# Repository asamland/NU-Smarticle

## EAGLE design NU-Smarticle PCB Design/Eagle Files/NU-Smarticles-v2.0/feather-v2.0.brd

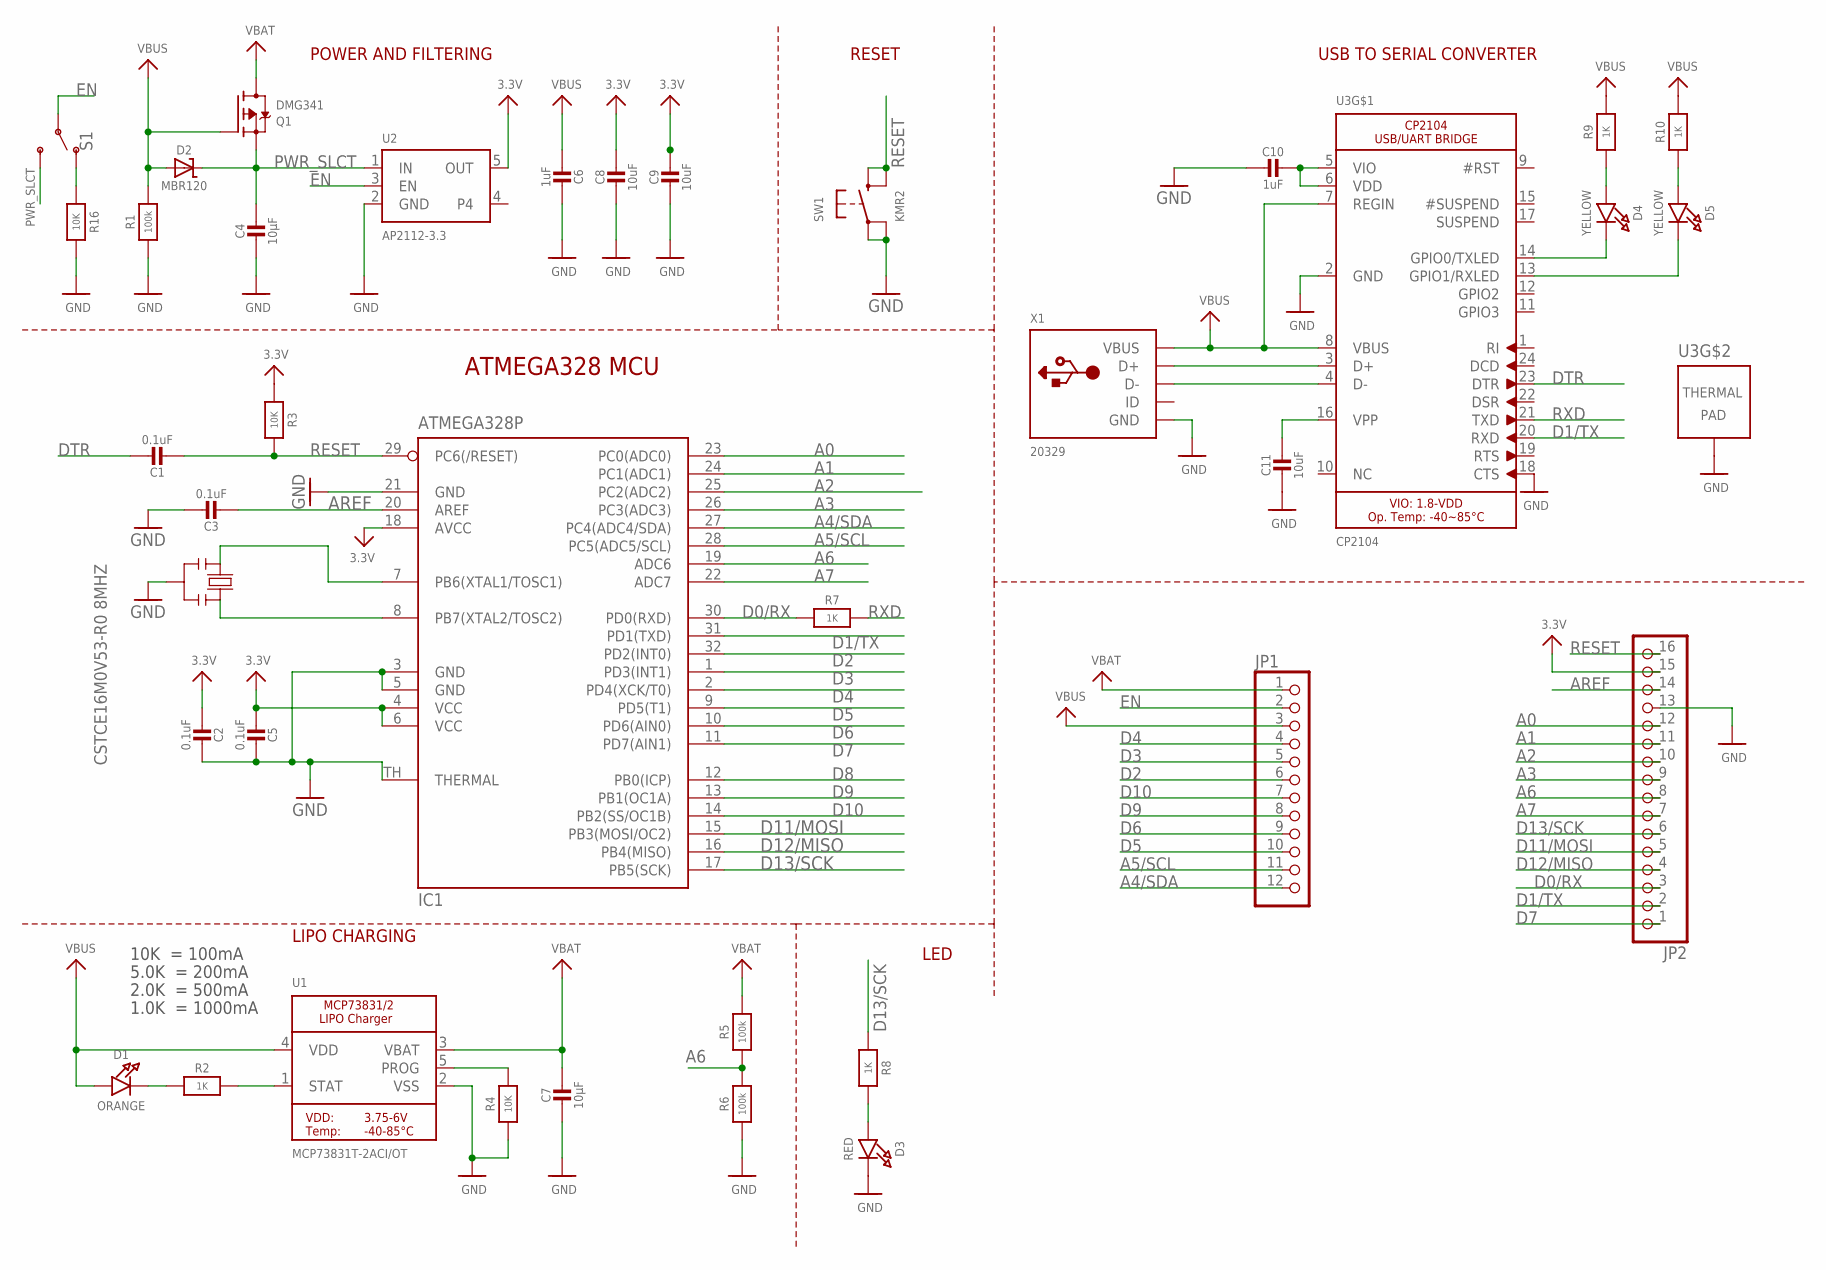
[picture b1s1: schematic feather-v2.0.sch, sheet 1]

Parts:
C1, C2, C3, C5: 0.1uF; _0603MP
C4, C7: 10µF; _0603MP
C6, C10: 1uF; _0603MP
C8, C9, C11: 10uF; _0603MP
D1: ORANGE; CHIPLED_0603_NOOUTLINE
D2: MBR120; SOD-323
D3: RED; CHIPLED_0603_NOOUTLINE
D4, D5: YELLOW; CHIPLED_0603_NOOUTLINE
IC1: ATMEGA328P; MLF32-TH
JP1: HEADER-1X12; 1X12_ROUND
JP2: HEADER-1X16ROUND; 1X16_ROUND
Q1: DMG341; SOT23-R
R1, R5, R6: 100k; _0603MP
R2, R7, R8, R9, R10: 1K; _0603MP
R3, R4, R16: 10K; _0603MP
S1: SWITCH-SPDT-SMD-RIGHT-ANGLE; SWITCH_SPST_SMD_A
SW1: KMR2; BTN_KMR2_4.6X2.8
U1: MCP73831T-2ACI/OT; SOT23-5
U2: AP2112-3.3; SOT23-5
U3: CP2104; QFN24_4MM_SMSC
X1: 20329; 4UCONN_20329_V2
Y1: CSTCE16M0V53-R0 8MHZ; RESONATOR

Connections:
3.3V: C2.2, C5.2, C8.1, C9.1, IC1.4 (VCC), IC1.6 (VCC), IC1.18 (AVCC), JP2.15, R3.2, U2.5 (OUT); also elsewhere on the board
A0: IC1.23 (PC0(ADC0)), JP2.12; also elsewhere on the board
A1: IC1.24 (PC1(ADC1)), JP2.11; also elsewhere on the board
A2: IC1.25 (PC2(ADC2)), JP2.10; also elsewhere on the board
A3: IC1.26 (PC3(ADC3)), JP2.9; also elsewhere on the board
A4/SDA: IC1.27 (PC4(ADC4/SDA)), JP1.12
A5/SCL: IC1.28 (PC5(ADC5/SCL)), JP1.11
A6: IC1.19 (ADC6), JP2.8, R5.1, R6.2
A7: IC1.22 (ADC7), JP2.7
AREF: C3.2, IC1.20 (AREF), JP2.14
D0/RX: IC1.30 (PD0(RXD)), JP2.3, R7.1
D1/TX: IC1.31 (PD1(TXD)), JP2.2, U3.20 (RXD)
D2: IC1.32 (PD2(INT0)), JP1.6; also elsewhere on the board
D3: IC1.1 (PD3(INT1)), JP1.5; also elsewhere on the board
D4: IC1.2 (PD4(XCK/T0)), JP1.4; also elsewhere on the board
D5: IC1.9 (PD5(T1)), JP1.10
D6: IC1.10 (PD6(AIN0)), JP1.9
D7: IC1.11 (PD7(AIN1)), JP2.1; also elsewhere on the board
D8: IC1.12 (PB0(ICP))
D9: IC1.13 (PB1(OC1A)), JP1.8
D10: IC1.14 (PB2(SS/OC1B)), JP1.7; also elsewhere on the board
D11/MOSI: IC1.15 (PB3(MOSI/OC2)), JP2.5
D12/MISO: IC1.16 (PB4(MISO)), JP2.4
D13/SCK: IC1.17 (PB5(SCK)), JP2.6, R8.1
DTR: C1.1, U3.23 (DTR)
EN: JP1.2, S1.2, U2.3 (EN)
GND: C2.1, C3.1, C4.2, C5.1, C6.1, C7.2, C8.2, C9.2, C10.2, C11.2, D3.C, IC1.3 (GND), IC1.5 (GND), IC1.21 (GND), IC1.TH (THERMAL), JP2.13, R1.1, R4.1, R6.1, R16.1, SW1.A, SW1.A' (P1), U1.2 (VSS), U2.2 (GND), U3.2 (GND), U3.18 (CTS), U3.THERM (TP), X1.BASE@1 (GND), X1.BASE@2 (GND), X1.GND, X1.SPRT@1 (GND), X1.SPRT@2 (GND), X1.SPRT@3 (GND), X1.SPRT@4 (GND), Y1.2; also elsewhere on the board
unnamed: D1.C, R2.1
unnamed: U3.3 (D+), X1.D+
unnamed: R2.2, U1.1 (STAT)
unnamed: R4.2, U1.5 (PROG)
unnamed: D3.A, R8.2
unnamed: U3.4 (D-), X1.D-
unnamed: R16.2, S1.1 (O)
unnamed: D5.A, R10.1
unnamed: D4.A, R9.1
unnamed: C10.1, U3.5 (VIO), U3.6 (VDD)
unnamed: C11.1, U3.16 (VPP)
PWR_SLCT: C4.1, D2.C, Q1.2 (S), S1.3 (S), U2.1 (IN)
RESET: C1.2, IC1.29 (PC6(/RESET)), JP2.16, R3.1, SW1.B (S), SW1.B' (S1)
RXD: R7.2, U3.21 (TXD)
RXLED: D5.C, U3.13 (GPIO1/RXLED)
TXLED: D4.C, U3.14 (GPIO0/TXLED)
VBAT: C7.1, JP1.1, Q1.3 (D), R5.2, U1.3 (VBAT); also elsewhere on the board
VBUS: C6.2, D1.A, D2.A, JP1.3, Q1.1 (G), R1.2, R9.2, R10.2, U1.4 (VDD), U3.7 (REGIN), U3.8 (VBUS), X1.VBUS
XTAL1: IC1.8 (PB7(XTAL2/TOSC2)), Y1.3
XTAL2: IC1.7 (PB6(XTAL1/TOSC1)), Y1.1

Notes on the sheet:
POWER AND FILTERING
RESET
10K = 100mA
5.0K = 200mA
2.0K = 500mA
1.0K = 1000mA
USB TO SERIAL CONVERTER
LIPO CHARGING
LED
ATMEGA328 MCU

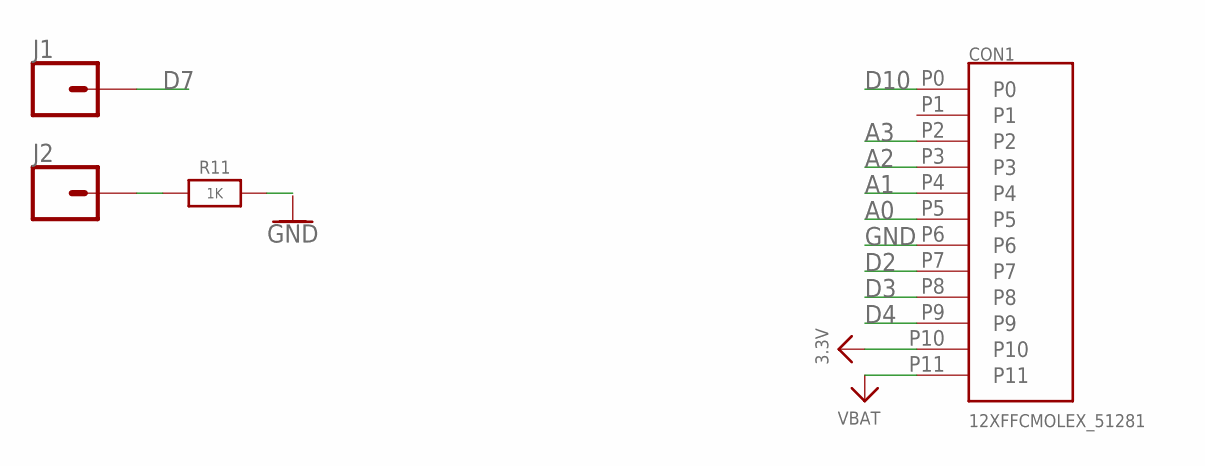
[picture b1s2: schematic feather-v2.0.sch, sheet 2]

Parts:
CON1: 12XFFCMOLEX_51281; MOLEX_51281-1294
J1, J2: CONN_01PTH_NO_SILK_YES_STOP; 1X01_NO_SILK
R11: 1K; _0603MP

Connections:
3.3V: CON1.P10; also elsewhere on the board
A0: CON1.P5; also elsewhere on the board
A1: CON1.P4; also elsewhere on the board
A2: CON1.P3; also elsewhere on the board
A3: CON1.P2; also elsewhere on the board
D2: CON1.P7; also elsewhere on the board
D3: CON1.P8; also elsewhere on the board
D4: CON1.P9; also elsewhere on the board
D7: J1.1; also elsewhere on the board
D10: CON1.P0; also elsewhere on the board
GND: CON1.P6; also elsewhere on the board
unnamed: J2.1, R11.1
VBAT: CON1.P11; also elsewhere on the board

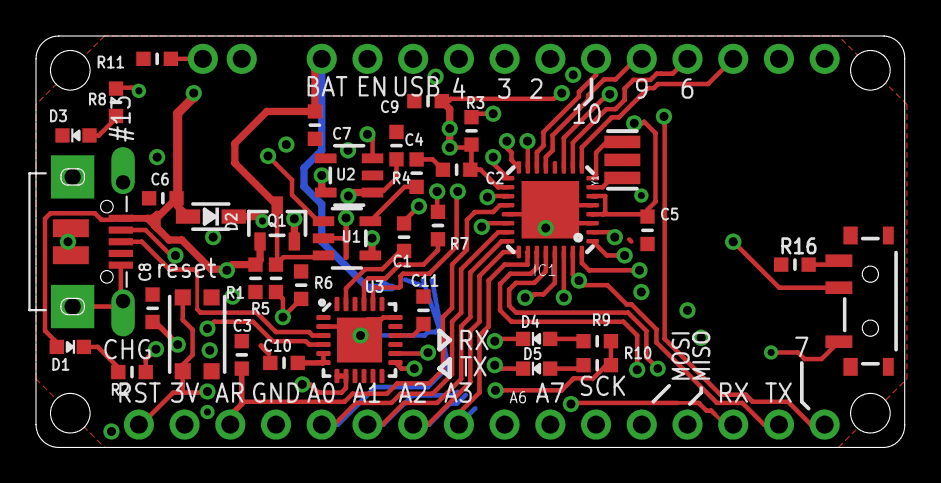
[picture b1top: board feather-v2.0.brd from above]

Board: 4 copper layers, 48.3 x 22.9 mm, 42 parts (1 on the bottom side), 47 nets.

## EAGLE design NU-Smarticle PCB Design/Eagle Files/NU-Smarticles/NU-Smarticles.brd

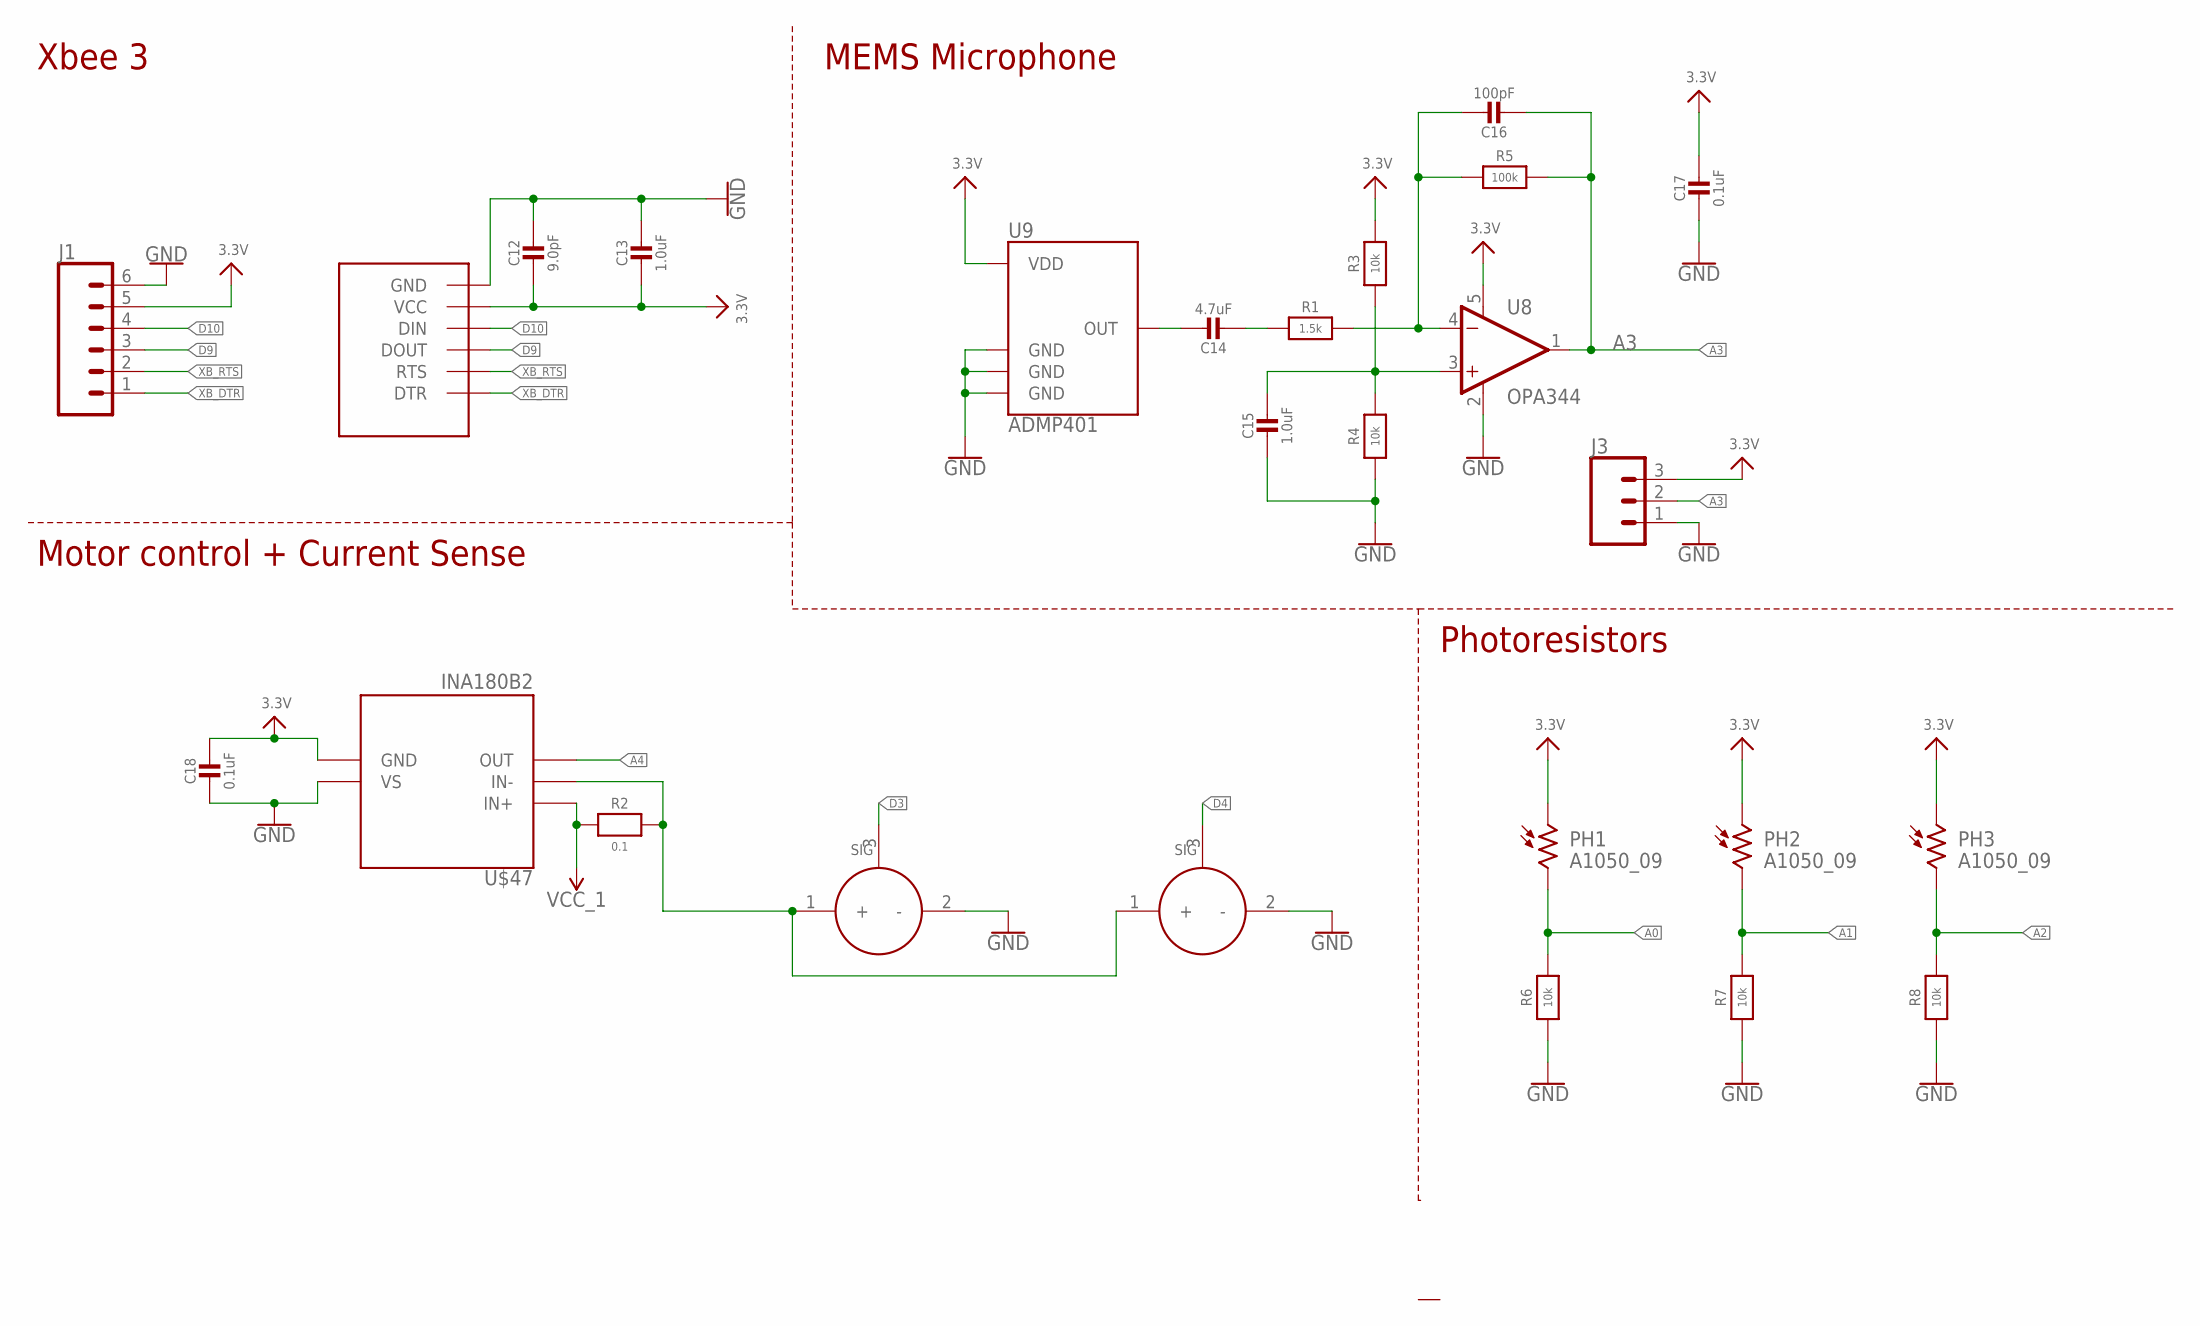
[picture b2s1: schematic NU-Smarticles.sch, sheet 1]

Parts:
C12: 9.0pF; _0402MP
C13, C15: 1.0uF; _0402MP
C14: 4.7uF; _0402MP
C16: 100pF; _0402MP
C17, C18: 0.1uF; _0402MP
J1: CONN_06NO_SILK_FEMALE_PTH; 1X06_NO_SILK
J3: CONN_03; 1X03
PH1, PH2, PH3: A1050_09; T0-46-A10XX
R1: 1.5k; _0402MP
R2: 0.1; _0603MP
R3, R4, R6, R7, R8: 10k; _0402MP
R5: 100k; _0402MP
U8: OPA344; SOT23-5
U9: ADMP401
U$1, U$46: SERVO; 1X03_SERVO
U$2: XBEE3; XBEE3_MICRO
U$47: INA180B2; SOT23-5

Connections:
3.3V: C12.2, C13.2, C17.1, C18.1, J1.5, J3.3, PH1.1, PH2.1, PH3.1, R3.2, U8.5 (V+), U9.5 (VDD), U$2.VCC, U$47.2 (GND); also elsewhere on the board
A0: PH1.2, R6.2; also elsewhere on the board
A1: PH2.2, R7.2; also elsewhere on the board
A2: PH3.2, R8.2; also elsewhere on the board
A3: C16.2, J3.2, R5.2, U8.1 (OUT); also elsewhere on the board
A4: U$47.4 (OUT); also elsewhere on the board
D3: U$1.3 (SIG); also elsewhere on the board
D4: U$46.3 (SIG); also elsewhere on the board
D9: J1.3, U$2.DOUT/DIO13 (DOUT); also elsewhere on the board
D10: J1.4, U$2.DIN/CONFIG/DIO14 (DIN); also elsewhere on the board
GND: C12.1, C13.1, C15.2, C17.2, C18.2, J1.6, J3.1, R4.1, R6.1, R7.1, R8.1, U8.2 (V-), U9.2 (GND), U9.4 (GND), U9.6 (GND), U$1.2 (-), U$2.GND1 (GND), U$46.2 (-), U$47.5 (VS); also elsewhere on the board
unnamed: R2.2, U$1.1 (+), U$46.1 (+), U$47.3 (IN-)
unnamed: C14.1, U9.1 (OUT)
unnamed: C16.1, R1.2, R5.1, U8.4 (-IN)
unnamed: C14.2, R1.1
unnamed: C15.1, R3.1, R4.2, U8.3 (+IN)
VCC_1: R2.1, U$47.1 (IN+); also elsewhere on the board
XB_DTR: J1.1, U$2.DTR/SLEEP_RQ/DIO8 (DTR)
XB_RTS: J1.2, U$2.RTS/DIO6 (RTS)

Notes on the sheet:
Xbee 3
Photoresistors
Motor control + Current Sense
MEMS Microphone

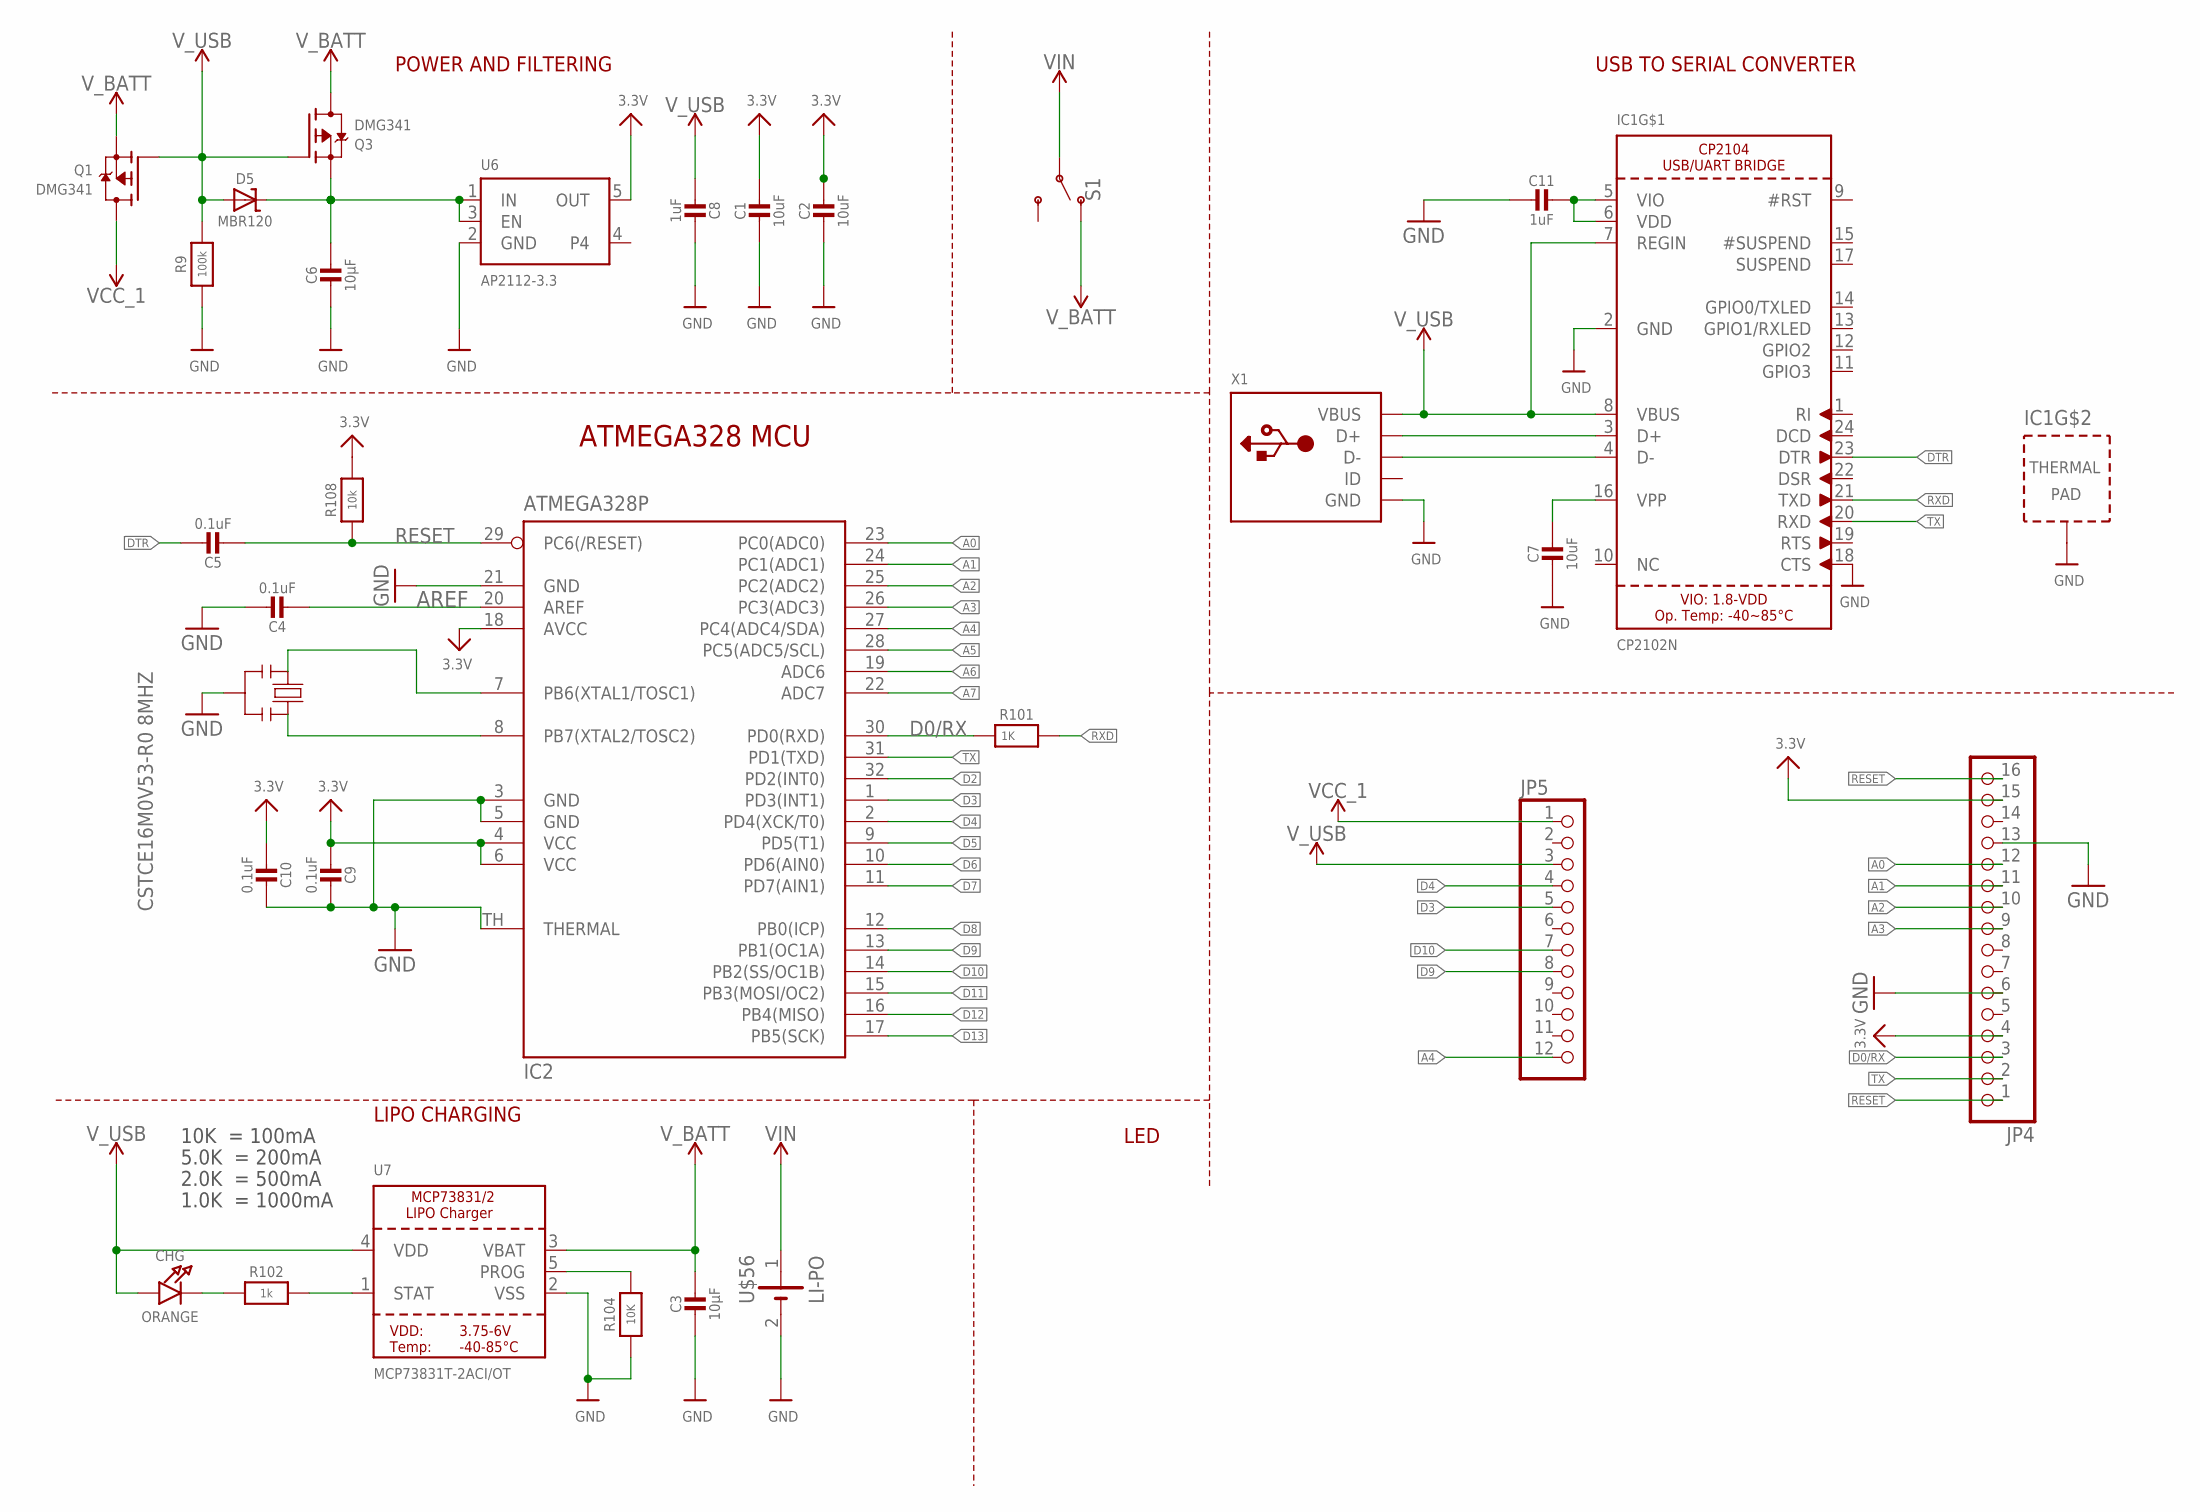
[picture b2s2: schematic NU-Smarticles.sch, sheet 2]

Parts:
C1, C2, C7: 10uF; _0402MP
C3, C6: 10µF; _0402MP
C4, C5, C9, C10: 0.1uF; _0402MP
C8, C11: 1uF; _0402MP
CHG: ORANGE; CHIPLED_0603
D5: MBR120; SOD-523
IC1: CP2102N; QFN24_4MM_SMSC
IC2: ATMEGA328P; MLF32-TH
JP4: HEADER-1X16ROUND; 1X16_ROUND
JP5: HEADER-1X12; 1X12_ROUND
Q1, Q3: DMG341; SOT23-R
R9: 100k; _0402MP
R101: 1K; _0402MP
R102: 1k; _0402MP
R104: 10K; _0402MP
R108: 10k; _0402MP
S1: SWITCH-SPDT-SMD-AYZ0202; SWITCH_DPDT_SMD_AYZ0202
U6: AP2112-3.3; SOT23-5
U7: MCP73831T-2ACI/OT; SOT23-5
U$56: LI-PO; 1X02_BATT
X1: USBMICRO_20329; 4UCONN_20329
Y2: CSTCE16M0V53-R0 8MHZ; RESONATOR

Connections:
3.3V: C1.1, C2.1, C9.2, C10.2, IC2.4 (VCC), IC2.6 (VCC), IC2.18 (AVCC), JP4.4, JP4.15, R108.2, U6.5 (OUT); also elsewhere on the board
A0: IC2.23 (PC0(ADC0)), JP4.12; also elsewhere on the board
A1: IC2.24 (PC1(ADC1)), JP4.11; also elsewhere on the board
A2: IC2.25 (PC2(ADC2)), JP4.10; also elsewhere on the board
A3: IC2.26 (PC3(ADC3)), JP4.9; also elsewhere on the board
A4: IC2.27 (PC4(ADC4/SDA)), JP5.12; also elsewhere on the board
A5: IC2.28 (PC5(ADC5/SCL))
A6: IC2.19 (ADC6)
A7: IC2.22 (ADC7)
AREF: C4.2, IC2.20 (AREF)
D0/RX: IC2.30 (PD0(RXD)), JP4.3, R101.1
D2: IC2.32 (PD2(INT0))
D3: IC2.1 (PD3(INT1)), JP5.5; also elsewhere on the board
D4: IC2.2 (PD4(XCK/T0)), JP5.4; also elsewhere on the board
D5: IC2.9 (PD5(T1))
D6: IC2.10 (PD6(AIN0))
D7: IC2.11 (PD7(AIN1))
D8: IC2.12 (PB0(ICP))
D9: IC2.13 (PB1(OC1A)), JP5.8; also elsewhere on the board
D10: IC2.14 (PB2(SS/OC1B)), JP5.7; also elsewhere on the board
D11: IC2.15 (PB3(MOSI/OC2))
D12: IC2.16 (PB4(MISO))
D13: IC2.17 (PB5(SCK))
DTR: C5.1, IC1.23 (DTR)
GND: C1.2, C2.2, C3.2, C4.1, C6.2, C7.2, C8.1, C9.1, C10.1, C11.2, IC1.2 (GND), IC1.18 (CTS), IC1.THERM (TP), IC2.3 (GND), IC2.5 (GND), IC2.21 (GND), IC2.TH (THERMAL), JP4.6, JP4.13, R9.1, R104.1, U6.2 (GND), U7.2 (VSS), U$56.2 (-), X1.BASE@1 (GND), X1.BASE@2 (GND), X1.GND, X1.SPRT@1 (GND), X1.SPRT@2 (GND), X1.SPRT@3 (GND), X1.SPRT@4 (GND), Y2.2; also elsewhere on the board
unnamed: IC1.3 (D+), X1.D+
unnamed: IC1.4 (D-), X1.D-
unnamed: CHG.C, R102.1
unnamed: R102.2, U7.1 (STAT)
unnamed: R104.2, U7.5 (PROG)
unnamed: C6.1, D5.K (C), Q3.2 (S), U6.1 (IN), U6.3 (EN)
unnamed: C11.1, IC1.5 (VIO), IC1.6 (VDD)
unnamed: C7.1, IC1.16 (VPP)
RESET: C5.2, IC2.29 (PC6(/RESET)), JP4.1, JP4.16, R108.1
RXD: IC1.21 (TXD), R101.2
TX: IC1.20 (RXD), IC2.31 (PD1(TXD)), JP4.2
VCC_1: JP5.1, Q1.3 (D); also elsewhere on the board
VIN: S1.2, U$56.1 (+)
V_BATT: C3.1, Q1.2 (S), Q3.3 (D), S1.1 (O), U7.3 (VBAT)
V_USB: C8.2, CHG.A, D5.A, IC1.7 (REGIN), IC1.8 (VBUS), JP5.3, Q1.1 (G), Q3.1 (G), R9.2, U7.4 (VDD), X1.VBUS
XTAL1: IC2.8 (PB7(XTAL2/TOSC2)), Y2.3
XTAL2: IC2.7 (PB6(XTAL1/TOSC1)), Y2.1

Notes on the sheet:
POWER AND FILTERING
10K = 100mA
5.0K = 200mA
2.0K = 500mA
1.0K = 1000mA
USB TO SERIAL CONVERTER
LIPO CHARGING
LED
ATMEGA328 MCU

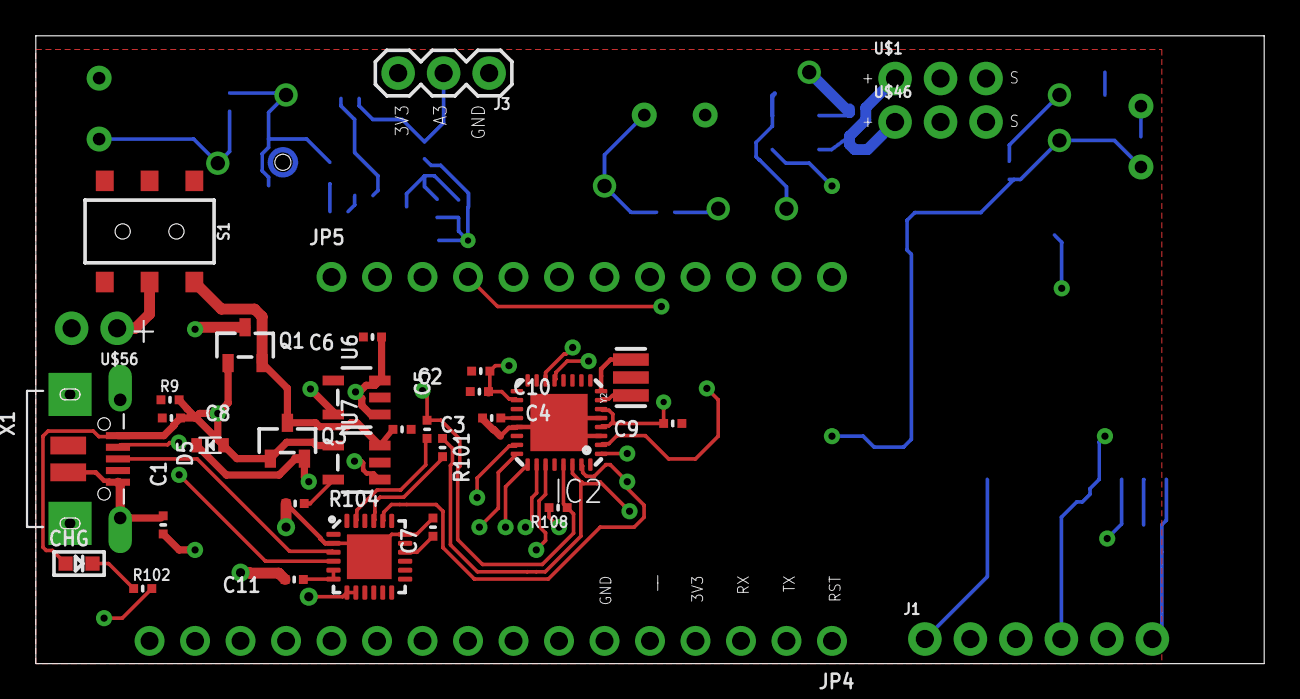
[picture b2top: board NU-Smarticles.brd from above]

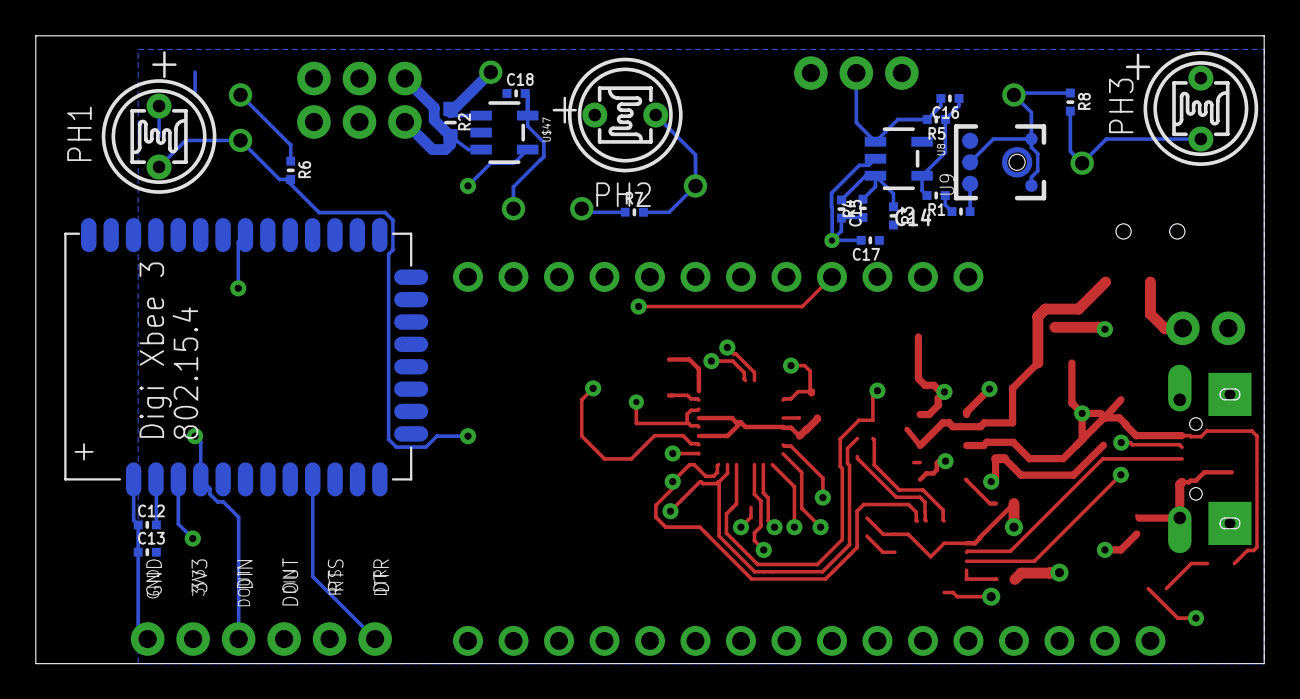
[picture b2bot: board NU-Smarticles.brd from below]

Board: 4 copper layers, 68.6 x 35.1 mm, 56 parts (22 on the bottom side), 38 nets.

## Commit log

2019-03-09 datasheets
2019-03-09 adafruit feather 328p
2019-03-09 Arduino Pro Mini
2019-03-09 FTDI Basic
2019-03-09 ADMP401
2019-03-09 schematics and boards
2019-03-09 board
2019-03-09 old library
2019-07-25 include v2 Smarticles
2019-07-26 smarticle test code
2019-07-26 Xbee Docs
2019-07-31 solidworks
2019-07-31 updated case3
2019-08-01 .py worl
2019-08-06 Create SmarticleSwarm.py
    beginnings of our own smarticle module
2019-08-06 starting work on plotting
2019-08-06 xbee config info
2019-08-06 network update
2019-08-06 change to Xbee class
2019-08-08 code organization
2019-08-12 libraries work
2019-08-12 interp msg work
2019-08-13 updated python modules
2019-08-13 update cpp files
2019-08-13 python library work
2019-08-14 library updates
2019-08-14 added compression for GI transmission
2019-08-14 python code update
2019-08-15 stable gait interpolation for inital experiments
2019-08-15 experiment work
2019-08-19 Update .gitignore
    ignore .pyc files
2019-08-19 Updated Doc
    updated documentation for python files
2019-08-21 organized files
2019-09-27 delete smarticle code
    smarticle code now maintained on SmarticleNU
2019-09-27 renamed eagle project
2019-09-27 eagle v2 work
2019-09-27 rename folders
2019-09-27 rename folder
2019-09-27 renamed folder
2019-10-22 added holes for securing feather board
2019-10-22 eagle work and files added
2019-10-24 cleaned up solidworks directory
2019-10-24 spill ring added
2019-10-24 smarticle case updates
    1) make space bigger for feather board
    2) make holes bigger for arms
    3)prevent beads from seeping in by adding guards
2019-10-24 spiked ring
2019-11-01 arm CAD
2019-11-01 inventory
2019-11-01 eagle files
2019-11-01 more arms
2019-11-01 more arm
2019-11-04 arm is done!
2019-11-05 arm and inventory
2019-11-21 case changes
    1) changed case to make it easier to put arms in
    2) made changes to make it easier to put in feather board
2019-11-24 hardware work
2019-12-10 small spill ring
2020-01-08 cad work for tommy
2020-01-10 inventory update and april tags
2020-01-16 herding ring
2020-01-16 220mm ring
2020-01-19 230mm ring in thirds
2020-01-20 192mm ring
2020-01-23 new rings
2020-01-23 new ring
2020-01-24 updated inventory
2020-01-24 200mm ring
2020-01-31 apriltags for ring added
2020-02-05 soldiworks changes
2020-02-05 URDF
2020-02-06 new urdf
2020-02-06 ring stl
2020-02-07 obj file
2020-02-07 new simulation cad
2020-02-17 organize solidworks folder
2020-03-05 update inventory, eagle
2020-03-06 hope this is ok
2020-03-08 cad for light holder
2020-03-09 more cad
2020-03-09 more cad
    revisions to light holding piece after printing prototypes
2020-03-31 BOMs

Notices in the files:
parts and their libraries:
SparkFun-Connectors: Licensing: Creative Commons ShareAlike 4.0 International - https://creativecommons.org/licenses/by-sa/4.0
microbuilder: This work is placed in the public domain, and may be freely used for commercial and non-commercial work with the following conditions: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
